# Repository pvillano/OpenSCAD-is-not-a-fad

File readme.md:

See https://www.printables.com/pvillano

library imports currently not working

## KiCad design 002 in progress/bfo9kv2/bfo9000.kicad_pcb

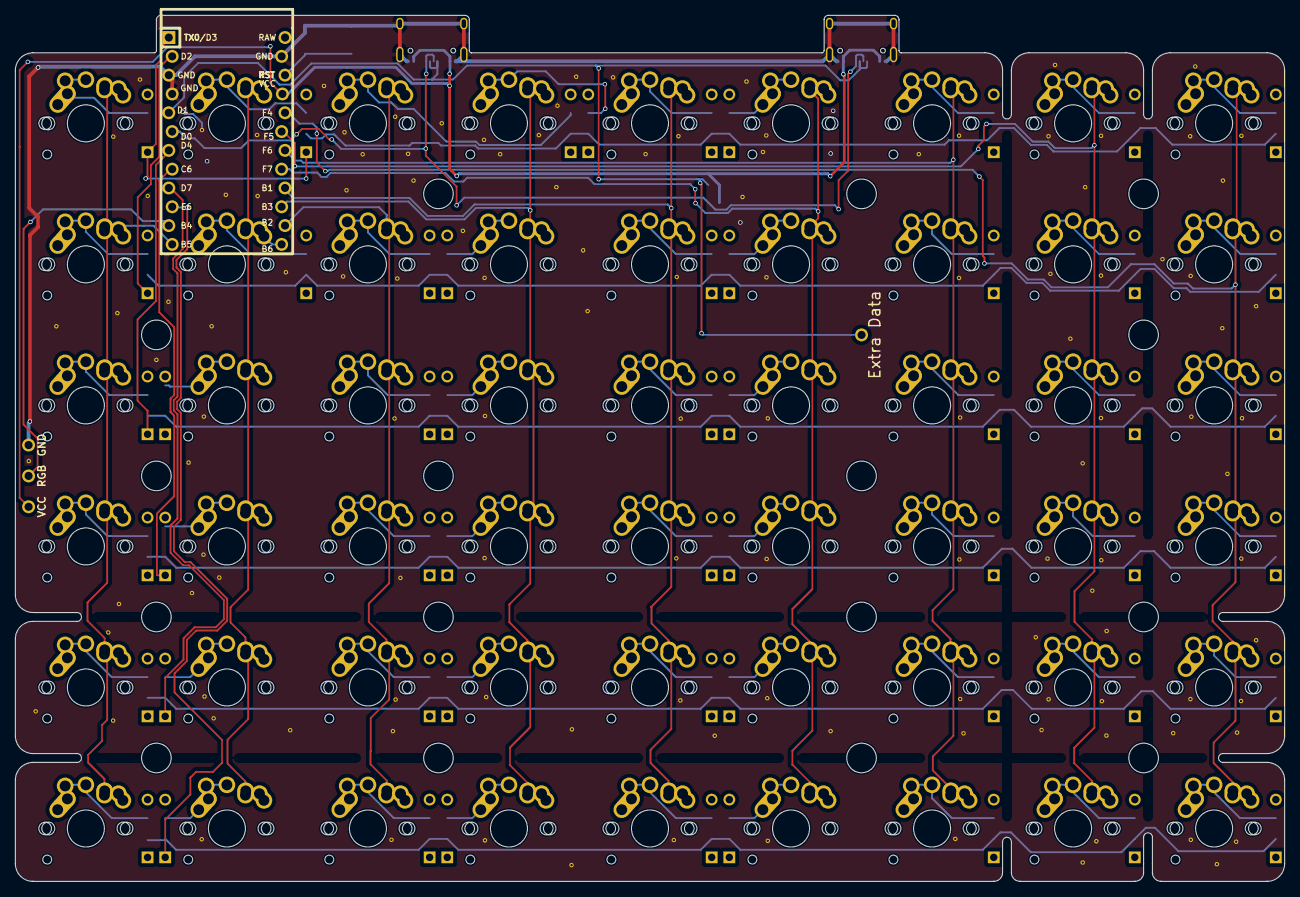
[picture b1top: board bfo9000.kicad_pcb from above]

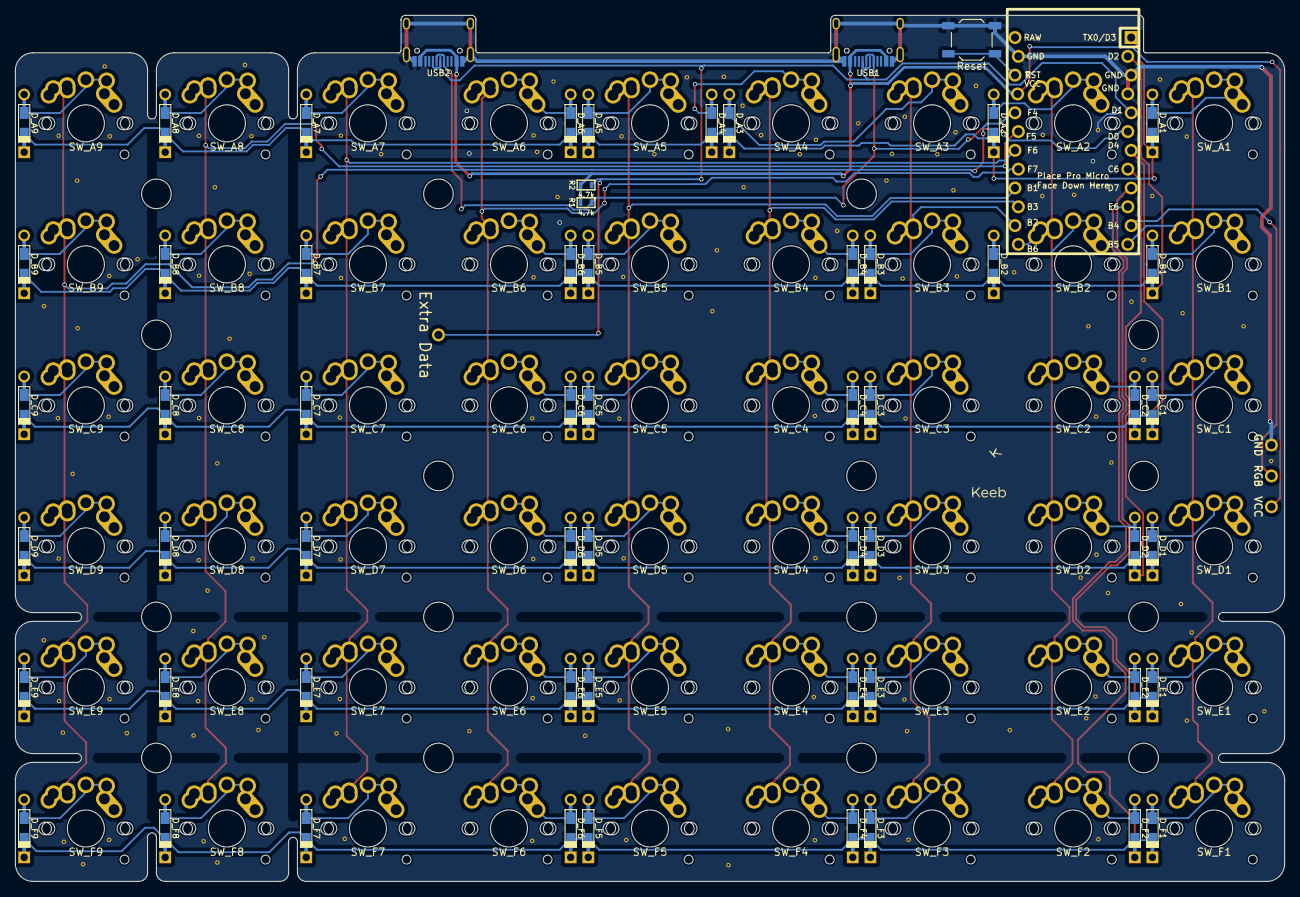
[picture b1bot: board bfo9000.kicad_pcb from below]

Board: 2 copper layers, 171.5 x 117.0 mm, 134 parts (5 on the bottom side), 75 nets.

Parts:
D_A1, D_A2, D_A3, D_A4, D_A5, D_A6, D_A7, D_A8, D_A9: D; Diode-Hybrid-Back
D_B1, D_B2, D_B3, D_B4, D_B5, D_B6, D_B7, D_B8, D_B9: D; Diode-Hybrid-Back
D_C1, D_C2, D_C3, D_C4, D_C5, D_C6, D_C7, D_C8, D_C9: D; Diode-Hybrid-Back
D_D1, D_D2, D_D3, D_D4, D_D5, D_D6, D_D7, D_D8, D_D9: D; Diode-Hybrid-Back
D_E1, D_E2, D_E3, D_E4, D_E5, D_E6, D_E7, D_E8, D_E9: D; Diode-Hybrid-Back
D_F1, D_F2, D_F3, D_F4, D_F5, D_F6, D_F7, D_F8, D_F9: D; Diode-Hybrid-Back
H1, H2, H3, H4, H4#2, H4#3, H4#4, H4#5, H4#6, H4#7, H4#8, H4#9, H4#10, H4#11, H4#12, H4#13: Hole; MountingHole_4mm
R1, R2: 4.7k; R_0603
SW_A1, SW_A2, SW_A3, SW_A4, SW_A5, SW_A6, SW_A7, SW_A8, SW_A9: SW_Push; MX-Alps-Choc_V1V2_KS-33-1U-NoLED-Alt
SW_B1, SW_B2, SW_B3, SW_B4, SW_B5, SW_B6, SW_B7, SW_B8, SW_B9: SW_Push; MX-Alps-Choc_V1V2_KS-33-1U-NoLED-Alt
SW_C1, SW_C2, SW_C3, SW_C4, SW_C5, SW_C6, SW_C7, SW_C8, SW_C9: SW_Push; MX-Alps-Choc_V1V2_KS-33-1U-NoLED-Alt
SW_D1, SW_D2, SW_D3, SW_D4, SW_D5, SW_D6, SW_D7, SW_D8, SW_D9: SW_Push; MX-Alps-Choc_V1V2_KS-33-1U-NoLED-Alt
SW_E1, SW_E2, SW_E3, SW_E4, SW_E5, SW_E6, SW_E7, SW_E8, SW_E9: SW_Push; MX-Alps-Choc_V1V2_KS-33-1U-NoLED-Alt
SW_F1, SW_F2, SW_F3, SW_F4, SW_F5, SW_F6, SW_F7, SW_F8, SW_F9: SW_Push; MX-Alps-Choc_V1V2_KS-33-1U-NoLED-Alt
SW_RESET1: Reset; SW_SPST_TL3342
TP1: Extra Data; SinglePad
TP2: RGB; SinglePad
TP3: VCC; SinglePad
TP4: GND; SinglePad
U1: ProMicro; ArduinoProMicro-ZigZag
USB1, USB2: HRO-TYPE-C-31-M-12; HRO-TYPE-C-31-M-12-Assembly

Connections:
Col1: SW_A1.1, SW_B1.1, SW_C1.1, SW_D1.1, SW_E1.1, SW_F1.1, U1.12 (9/PB5)
Col2: SW_A2.1, SW_B2.1, SW_C2.1, SW_D2.1, SW_E2.1, SW_F2.1, U1.13 (10/PB6)
Col3: SW_A3.1, SW_B3.1, SW_C3.1, SW_D3.1, SW_E3.1, SW_F3.1, U1.14 (16/PB2)
Col4: SW_A4.1, SW_B4.1, SW_C4.1, SW_D4.1, SW_E4.1, SW_F4.1, U1.15 (14/PB3)
Col5: SW_A5.1, SW_B5.1, SW_C5.1, SW_D5.1, SW_E5.1, SW_F5.1, U1.16 (15/PB1)
Col6: SW_A6.1, SW_B6.1, SW_C6.1, SW_D6.1, SW_E6.1, SW_F6.1, U1.17 (A0/PF7)
Col7: SW_A7.1, SW_B7.1, SW_C7.1, SW_D7.1, SW_E7.1, SW_F7.1, U1.18 (A1/PF6)
Col8: SW_A8.1, SW_B8.1, SW_C8.1, SW_D8.1, SW_E8.1, SW_F8.1, U1.19 (A2/PF5)
Col9: SW_A9.1, SW_B9.1, SW_C9.1, SW_D9.1, SW_E9.1, SW_F9.1, U1.20 (A3/PF4)
GND: SW_RESET1.2, TP4.1, U1.3 (GND), U1.4 (GND), U1.23 (GND), USB1.1 (GND), USB1.12 (GND), USB1.13 (SHIELD), USB2.1 (GND), USB2.12 (GND), USB2.13 (SHIELD)
unnamed: D_A1.2 (A), SW_A1.2
unnamed: D_A2.2 (A), SW_A2.2
unnamed: D_A3.2 (A), SW_A3.2
unnamed: D_A4.2 (A), SW_A4.2
unnamed: D_A5.2 (A), SW_A5.2
unnamed: D_A6.2 (A), SW_A6.2
unnamed: D_A7.2 (A), SW_A7.2
unnamed: D_A8.2 (A), SW_A8.2
unnamed: D_A9.2 (A), SW_A9.2
unnamed: D_B1.2 (A), SW_B1.2
unnamed: D_B2.2 (A), SW_B2.2
unnamed: D_B3.2 (A), SW_B3.2
unnamed: D_B4.2 (A), SW_B4.2
unnamed: D_B5.2 (A), SW_B5.2
unnamed: D_B6.2 (A), SW_B6.2
unnamed: D_B7.2 (A), SW_B7.2
unnamed: D_B8.2 (A), SW_B8.2
unnamed: D_B9.2 (A), SW_B9.2
unnamed: D_C1.2 (A), SW_C1.2
unnamed: D_C2.2 (A), SW_C2.2
unnamed: D_C3.2 (A), SW_C3.2
unnamed: D_C4.2 (A), SW_C4.2
unnamed: D_C5.2 (A), SW_C5.2
unnamed: D_C6.2 (A), SW_C6.2
unnamed: D_C7.2 (A), SW_C7.2
unnamed: D_C8.2 (A), SW_C8.2
unnamed: D_C9.2 (A), SW_C9.2
unnamed: D_D1.2 (A), SW_D1.2
unnamed: D_D2.2 (A), SW_D2.2
unnamed: D_D3.2 (A), SW_D3.2
unnamed: D_D4.2 (A), SW_D4.2
unnamed: D_D5.2 (A), SW_D5.2
unnamed: D_D6.2 (A), SW_D6.2
unnamed: D_D7.2 (A), SW_D7.2
unnamed: D_D8.2 (A), SW_D8.2
unnamed: D_D9.2 (A), SW_D9.2
unnamed: D_E1.2 (A), SW_E1.2
unnamed: D_E2.2 (A), SW_E2.2
unnamed: D_E3.2 (A), SW_E3.2
unnamed: D_E4.2 (A), SW_E4.2
unnamed: D_E5.2 (A), SW_E5.2
unnamed: D_E6.2 (A), SW_E6.2
unnamed: D_E7.2 (A), SW_E7.2
unnamed: D_E8.2 (A), SW_E8.2
unnamed: D_E9.2 (A), SW_E9.2
unnamed: D_F1.2 (A), SW_F1.2
unnamed: D_F2.2 (A), SW_F2.2
unnamed: D_F3.2 (A), SW_F3.2
unnamed: D_F4.2 (A), SW_F4.2
unnamed: D_F5.2 (A), SW_F5.2
unnamed: D_F6.2 (A), SW_F6.2
unnamed: D_F7.2 (A), SW_F7.2
unnamed: D_F8.2 (A), SW_F8.2
unnamed: D_F9.2 (A), SW_F9.2
unnamed: SW_RESET1.1, U1.22 (RST)
RGB: TP2.1, U1.11 (8/PB4)
RowA: D_A1.1 (K), D_A2.1 (K), D_A3.1 (K), D_A4.1 (K), D_A5.1 (K), D_A6.1 (K), D_A7.1 (K), D_A8.1 (K), D_A9.1 (K), U1.1 (TX0/PD3)
RowB: D_B1.1 (K), D_B2.1 (K), D_B3.1 (K), D_B4.1 (K), D_B5.1 (K), D_B6.1 (K), D_B7.1 (K), D_B8.1 (K), D_B9.1 (K), U1.2 (RX1/PD2)
RowC: D_C1.1 (K), D_C2.1 (K), D_C3.1 (K), D_C4.1 (K), D_C5.1 (K), D_C6.1 (K), D_C7.1 (K), D_C8.1 (K), D_C9.1 (K), U1.7 (4/PD4)
RowD: D_D1.1 (K), D_D2.1 (K), D_D3.1 (K), D_D4.1 (K), D_D5.1 (K), D_D6.1 (K), D_D7.1 (K), D_D8.1 (K), D_D9.1 (K), U1.8 (5/PC6)
RowE: D_E1.1 (K), D_E2.1 (K), D_E3.1 (K), D_E4.1 (K), D_E5.1 (K), D_E6.1 (K), D_E7.1 (K), D_E8.1 (K), D_E9.1 (K), U1.9 (6/PD7)
RowF: D_F1.1 (K), D_F2.1 (K), D_F3.1 (K), D_F4.1 (K), D_F5.1 (K), D_F6.1 (K), D_F7.1 (K), D_F8.1 (K), D_F9.1 (K), U1.10 (7/PE6)
SCL: R1.2, U1.6 (3/PD0), USB1.5 (DN2), USB1.7 (DN1), USB2.5 (DN2), USB2.7 (DN1)
SDA: R2.2, TP1.1, U1.5 (2/PD1), USB1.6 (DP1), USB1.8 (DP2), USB2.6 (DP1), USB2.8 (DP2)
VCC: R1.1, R2.1, TP3.1, U1.21 (VCC), USB1.2 (VBUS), USB1.11 (VBUS), USB2.2 (VBUS), USB2.11 (VBUS)

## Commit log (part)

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2021-02-13 removed stl
2021-02-13 a
    a
2021-02-15 make a project for thingiverse
2021-02-19 forgot to commit this?
2021-03-11 kb and cable and alarm clock
2021-03-21 yeah
2021-07-10 more
2021-07-10 prep triads for publishing
2021-07-11 publishing
2021-07-11 asfadf
2021-07-14 stls
2021-08-25 united methodist church
2021-08-25 useless
2021-08-25 name plate style
2021-08-25 increased margins and thickness
2021-08-25 more models
2021-11-05 backup of thingiverse downloads
2021-11-05 created soy sauce dish
2021-11-05 created topography print with supports
2021-11-05 desk organizer with first three modules
2021-11-05 through hole diode bending jig
2021-11-05 flexitailgear fan grilles
2021-11-05 v0 of flexspline
2021-11-05 prototype zero
2021-11-06 tests for minimum number of teeth missing
2021-11-07 first prototype, too stiff, teeth to small, thread too big
2021-11-08 added readme
2021-11-11 added comments
2021-11-11 published
2021-11-11 egg crate v2
2021-11-11 egg crate v3
2021-11-12 published soy sus
2021-11-12 new version of bfo9k
2021-11-16 adjustments to slop of bfo9k
2021-11-22 "final" version of case
2021-11-22 new fume extractor
2021-11-22 halloween headband
2021-11-22 screw fit tester
2021-11-22 I printed it bacwards the first time
2021-11-22 a lil case for my kvm/usb hub to keep my desk a little neater
2021-12-01 vase mode strainer
2021-12-01 Thingiverse customizer is bad
2021-12-03 updated for publishing
2021-12-03 published fume extractor
2022-01-14 new model
2022-01-18 save pre trash
2022-01-18 remove dumb desk organizer
2022-01-18 LockedForge Designs
2022-01-18 v0 lens filter glasses
2022-01-18 made a mask dispenser
2022-01-18 shim for chandelier
2022-01-19 more lockedforge modules
2022-04-08 v1 of draining travel soap bars
2022-04-27 finished publishing, added screenshots
2022-04-27 prep colorado for publishing
2022-04-27 published colorado
2022-04-27 published d6 mmu
2022-04-27 deleted redundant
2022-04-27 published d12
2022-04-27 mask tower image
2022-04-27 original draft of mmu cover
2022-04-27 fixed holes being covered up
2022-04-27 preped mmu cover for publishing
2022-04-27 published mmu cover
2022-05-02 v2 of soap bar holder - more problems
2022-05-02 v2 of soap bar holder - more problems, more thoughts
2022-05-02 soap holder done except magnets
2022-05-05 remove abandoned
2022-05-06 added magnets, compatibility for older openscad parser
2022-05-06 added real magnets and support blockers
2022-06-28 I have made a hex key, now to make a holder
2022-07-01 created test hex key holder
2022-07-01 added comments, better def for r_bend
2022-07-06 downloads idk
2022-07-06 locked forge
2022-07-06 formatting
2022-07-06 messing with prototype
2022-07-06 progress: stuff floating in space
2022-07-06 threadless linear actuators: simple and hard.
2022-07-06 progress: more stuff floating in space
2022-07-07 v0 dremel jig
2022-07-08 new approach to dremel jig
2022-07-08 new new approach to dremel jig
2022-07-08 new new new approach to dremel jig
2022-07-08 new new new new approach to dremel jig
2022-07-08 i forgor
2022-07-08 spacing seems off
2022-07-08 saucer v0
2022-07-08 saucer v1
2022-07-10 saucy saucer
2022-07-10 random stls
2022-07-10 hex key holder: smalled walls, moved ghost out of difference
2022-07-10 added imperial keys (kinda)
2022-07-10 filled in some gaps
2022-07-13 some downloads
2022-07-14 deleted things I'll never share or print again
2022-08-08 added another module to locked forge
2022-08-08 new downloads
2022-08-16 prototype knife sharpener jig
2022-08-18 fixed nail clippers module
2022-08-19 bar keepers lover WIP
2022-08-22 v0 canopy fix
2022-08-22 v1 canopy fix
2022-08-22 v3 canopy fix
2022-09-02 v0 paint filter
2022-09-03 v0.1 paint filter
2022-09-03 v2 forevermask
2022-09-03 canopy fix remove extra hole
2022-09-03 Revert "v2 forevermask"
    This reverts commit 91c6eaba2b3c208f4f7c860a4abd478ec049020f.
2022-09-03 v2 forevermask all changes
2022-09-14 I needed a funnel right away
2022-09-14 what's version control
2022-09-14 version 3 of paint filter funnel now printable
2022-09-14 thingies
2022-09-14 WIP double letters
2022-09-14 commit loose files
2022-09-14 deleted in prep for reorganization
2022-09-14 massive move/rename
2022-09-14 added floating files
2022-09-15 start of keycaps for hexagon keyboard
2022-09-19 finished keycap negative to functional and demo
2022-09-21 v2 spirograph
2022-09-21 chitubox sucks: a presentation
2022-09-21 sliced caliper pyramid
2022-09-21 downloaded gridfinity
2022-09-23 fractal organizer proof of concept
2022-09-23 clean up fractal organizer
2022-09-23 printed the organizer
2022-09-24 add photos to fractal organizer
2022-09-24 code cleanup for publishing
2022-09-24 added examples to fractal organizer
2022-09-25 added some thangs
2022-09-25 this happened but we shall soon pretend it didn't
2022-09-25 Revert "this happened but we shall soon pretend it didn't"
    This reverts commit 52c4c3347f81501193cd0fed089e9508d79da2ed.
2022-09-25 version 0 of el big boy carbon filter
2022-09-25 version 2 complete rewrite
2022-09-25 fixed problem with holes showing up on lid, rendered
2022-09-26 prototype tushfinity
2022-09-26 added gridfinity library
2022-09-26 moved chitubox sucks to published
2022-09-26 testing insert clearance
2022-09-26 export all utility script
2022-09-26 Asjust clearances, hide hidden, option for base or insert
2022-09-26 create parameter set file for tushfinity
2022-09-26 added multiple insert sizes
2022-09-26 rendered config options
2022-09-26 bugfixes for export_all.py
2022-09-26 move arg parsing and validation to function
2022-09-26 fix output dir
2022-09-26 fixed tushfinity.json, regenerated
2022-09-26 removed non-publication-worthy files
2022-09-26 prep cable clip for publishing
2022-09-26 rename cable clip for publishing
2022-09-26 move and rename old projects
2022-10-04 wip el big boy
2022-10-04 flying flying buttress closer
2022-10-04 simplified flying buttresses
2022-10-04 stash
2022-10-18 v0 shaving brush stand
2022-11-17 lazy filter v0
2022-11-19 solder holder v0
2022-11-20 solder holder v2
2022-11-20 went with more squarish design for shaving brush stand
2022-11-20 LED diffuser prusaproject
2022-11-20 demagnitizer technically finished
2022-11-20 downloads
2022-11-20 WIPs laying around
2022-11-20 I don't actually remember
2022-11-26 moved projects around based on status
2022-11-27 tape holder
2022-11-27 paint bottle holder v0
2022-11-27 paint bottle holder v0.1 testing
2022-12-11 tree feet v0
2022-12-11 backups of resin slicing configs
2022-12-13 first sencongd prints on resin
2022-12-13 unpublished egg crates for creation of v3
2022-12-13 collapsed egg crates
2022-12-13 tree feet v1 final
2022-12-13 lost most of my apes because i dropped a commit instead of the one big file in it. this is that file, zipped
2022-12-20 blergh
2022-12-20 newer, even slower rendering egg crate
2023-01-10 final family dice ig
2023-02-11 battery adapter v0
2023-04-24 forever container v3 alpha
2023-04-24 add paid directory to gitignore
2023-04-25 made forever container more printable
2023-04-25 variabled and minatured forever container for prototyping
2023-04-25 update threads to my version
2023-04-25 forever container v4 alpha
2023-04-25 forever container v4 beta
2023-09-29 updated business card info
2023-10-15 17 cube storage v0
2023-10-15 cutlery orgainizer
2023-10-15 fruit basket stabilizer
2023-10-15 paper towel holder
2023-10-15 renamed egg crate
2023-10-15 moved family dice to completed
2023-10-15 move tape padded box to completed
2023-10-15 battery adapter
2023-10-15 forever container progress
2023-10-15 printalbes and thingiverse downloads
2023-10-15 mooncake box divider
2023-11-06 magnet paper towel holder
2023-11-06 magnet paper towel holder v0.2
2023-11-06 magnet paper towel holder my cabinets are SHORT
2023-11-08 magnet paper towel holder fillets and supports
2023-11-28 right angle screwdriver case v0
2023-11-28 right angle screwdriver case v1
2023-11-28 magnetic paper towel holder finished
2023-11-28 magnetic paper towel holder moved
2023-11-28 last try radial
2023-11-29 linear case
2024-02-13 ready mooncake box divider for publishing
2024-03-08 nameplate v1 this won't batch fool
2024-03-08 organize and parallelize
2024-03-08 nameplate v0
2024-03-08 automate generation of nameplate.json
2024-03-08 nameplate v2 this should work
2024-03-08 imagine using the variables you declared
2024-03-08 optimize rendering and add mouse ears
2024-03-08 add single "clip" build
2024-03-11 Fix Widening being name length dependent. Adjust height to fit more on build plate Separate base thickness and label thickness for shorter print time. Remove differences in preview/render.
2024-03-11 add speed render features by default
2024-03-11 fixed/widened mouse ear
2024-03-12 nameplate w/ logo WIP
2024-03-15 quickly nest clips to better fit on build plate
2024-03-26 luban needs testing
2024-03-28 fix swapped blue and gold
2024-04-04 standing clip v0
2024-05-16 nameplate...changes
2024-05-17 added trio and a progress bar
2024-05-17 finished right angle screwdriver case.stl
2024-05-20 business card v2.0
2024-05-20 failed 180 bend
2024-05-22 increased thickness, added brim
2024-05-23 mattias phone holder slimmed
2024-05-23 heart dice proof of concept
2024-05-23 mattias phone holder v0
2024-05-23 mattias phone holder thin walled, full backplate, charger cutout
2024-05-23 mattias phone holder super sparse, minus charger hole
2024-05-23 o spacers
2024-05-24 more tests
2024-05-24 v3 WIP
2024-07-02 pk silverware organizer WIP
2024-07-09 download broken mmu parts
2024-07-09 spindrip v0
2024-07-25 chamfer plane skirt remover v2
2024-07-26 chamfer plane skirt remover v3
2024-07-26 chamfer plane skirt remover v4
2024-09-01 hexastix
2024-11-22 watering calendar WIP
2024-11-22 switch to poetry
2024-11-22 watering calendar v2
2025-02-27 bfo9k v2 WIP
2025-02-27 swap in gateron keys, add studs, add base base
2025-02-27 add gateron spec
2025-02-27 increase h to accommodate switch studs, add holes for studs, add holes for IO, flatten plate, make room for pins, better comments
2025-02-27 comments and formatting
2025-02-28 measure usb pcb, try slanted again
2025-02-28 unslant, countersink top holes and heat set insert bottom holes, delete stl
2025-03-01 smd allowance, disabled bfo "logo" cutout
2025-03-01 add reset button hole, fix $fn usages
2025-03-02 The usb pcb doesnt actually touch, and the usbc ports are longer than I measured
2025-03-04 v1 twister spinner
2025-03-04 radius != diameter
2025-03-07 less soldering margin lol, bring back tilt, add hole slop, remove magnets
2025-03-29 add usb pcb measurements, heatsets, rotate plate instead of base, tilt compensation, magnet holes, conditional, subtle slant
2025-03-29 fix error in thickness math, move magnet holes down
2025-03-29 oil labels
2025-03-29 fix smd divots, offset magnets
2025-10-14 danska tin gridfinity first print
2025-10-14 608 holder first print
2025-10-22 publish lampshade
2025-10-23 utensil cone v0
2025-10-23 utensil cone v1
2025-10-26 utensil cone final
2025-10-27 solid dice test 1 result: kinda! cone of go away did nothing. ball wobbled during second half.
2025-10-27 solid dice v2: too complicated to finish lol
2025-10-27 solid dice v3: too unstable
2025-10-27 solid dice v4: this one was overly strong, and failed because of an interaction between octoprint and pauses
2025-10-27 solid dice v5: broke a little because of weak joins of single extrusion walls. also loose
2026-01-09 drill guide with right measurements
2026-01-21 magnetic paper towel holder.scad stronger
2026-01-21 WIPs
2026-01-21 put downloads in separate folder
2026-01-22 convert to uv
2026-01-22 bedsinger v3
2026-01-22 turn off fan
2026-01-22 add cylinder test
2026-01-22 optimize the fastest direction
2026-01-22 tune to thirds and fifths
2026-01-22 tune to pentatonic
2026-01-22 a better sounding test file
2026-01-22 black formatting, handle corexy, comment instead of removing lines in dry run
2026-01-22 maybe handle arbirary param order and fix a bug
2026-01-26 orgainize
2026-01-26 magnetic tape marker dispenser v0
2026-01-30 laptop WIP
2026-05-06 images
